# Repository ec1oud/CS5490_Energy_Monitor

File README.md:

# UEXT AC Energy Monitor module

I'm developing this for use with an 
[Olimex board](https://www.olimex.com/Products/OLinuXino/RT5350F/RT5350F-OLinuXino-EVB/open-source-hardware)
that runs [OpenWrt](https://openwrt.org/toh/olimex/rt5350f-olinuxino-evb) and
has two GPIO-controlled relays, which I'm hoping to use as a pool pump
controller.  I want to be able to monitor the performance of the pool pump over
time, because this summer it started overheating and eventually failed.  It
would be nice to get an early warning when that's about to happen.  I was
searching and it seems that the 
[CS5490](https://www.cirrus.com/products/cs5490/) will fit the bill: it's 3.3V
powered, cheap enough, doesn't require much supporting circuitry, and works
with current transformers.  The little Olimex board ought to be a good
replacement for the old PC with a DS2413 relay connected to a DS9490 USB
adapter, that has been acting as a pool pump timer (and doing some other minor
home automation tasks) for a few years.

So far I have a working breakout board, designed with 
[KiCad](http://kicad-pcb.org/), that is successfully measuring AC current.  It
has a resistive voltage divider for measuring voltage too, but there is a
safety issue: the design requires connecting DC ground to the neutral wire,
while the other end of the voltage divider goes to line voltage.  Usually
embedded systems like this are kept "floating" behind a transformer or isolated
switching power supply.  I would prefer to measure the full 240VAC that the
pool pump runs on, for accurate power computation, but of course I'm not going
to connect the DC ground of this board (and consequently the ground of the
Olimex board) to a "hot" wire.  In either case, the isolation of the Ethernet
port would depend on the fact that (hopefully) the network jack is
transformer-coupled, because I certainly wouldn't want to cause ground loop
issues on the network either.

Measuring current might be good enough to monitor my pool pump (although it's
not satisfying not to get all the measurements this chip is capable of).  But
to really use it as an energy monitor for anything other than 120VAC US-type
circuits, an isolated design is needed.  I'm thinking my options are to let the
entire CS5490 chip run from an independent power supply and use optocouplers to
isolate the serial line, so that the Olimex board can have a floating DC
ground; or, run everything from a plain old step-down transformer, measure the
AC voltage coming from the transformer (before the rectifier), and calibrate
the CS5490 so that it thinks it's measuring the full AC voltage feeding the
transformer.  An AC brownout ought to result in a proportionately lower voltage
from the transformer; and I hope there is no phase difference significant
enough to affect the power computation.

It also turns out the RT5350F-OLinuXino-EVB has a design flaw: the 
[UEXT connector](https://www.olimex.com/Products/Modules/UEXT/) has a serial
port, but it's the same one that the OpenWrt firmware is using for the Linux
console!  So I can't use those serial lines for communicating with external
hardware (which I thought is supposed to be the main purpose of a UEXT
connector) unless I alter the firmware (or at least the kernel boot parameters)
to disable the serial console, which would also amount to "bricking" the board
if anything goes wrong with the network configuration.  But there's another
serial port on the 40-pin EXT4 connector.  So I designed my board to plug into
the UEXT connector, but now I need to redesign it to plug into the 40-pin
connector instead, which makes it less portable to other embedded systems.  And
also take care of the AC isolation problem somehow.

So now you know the caveats... you'd probably better not connect the line and
neutral screw terminals to anything, unless you know what you're doing.  But
measuring current with a current transformer is pretty safe AFAIK, and works
fine with this design.  I wrote a little test GUI with Qt to communicate with
the board using an FTDI adapter or something like that.  I also wrote another
test client using Lua 5.1 on the OpenWrt firmware, but it depends on being able
to use lua-rs232 at 600 baud (the default baud rate of the CS5490's serial
lines).  See 
[the issue about that](https://github.com/openwrt/packages/issues/10024).

A design for a 3D-printable DIN rail mounting solution is also included:

The hardware design is licensed under a 

[Creative Commons Attribution-ShareAlike 4.0 International License](http://creativecommons.org/licenses/by-sa/4.0/)
.

The software has a GPLv3 license.

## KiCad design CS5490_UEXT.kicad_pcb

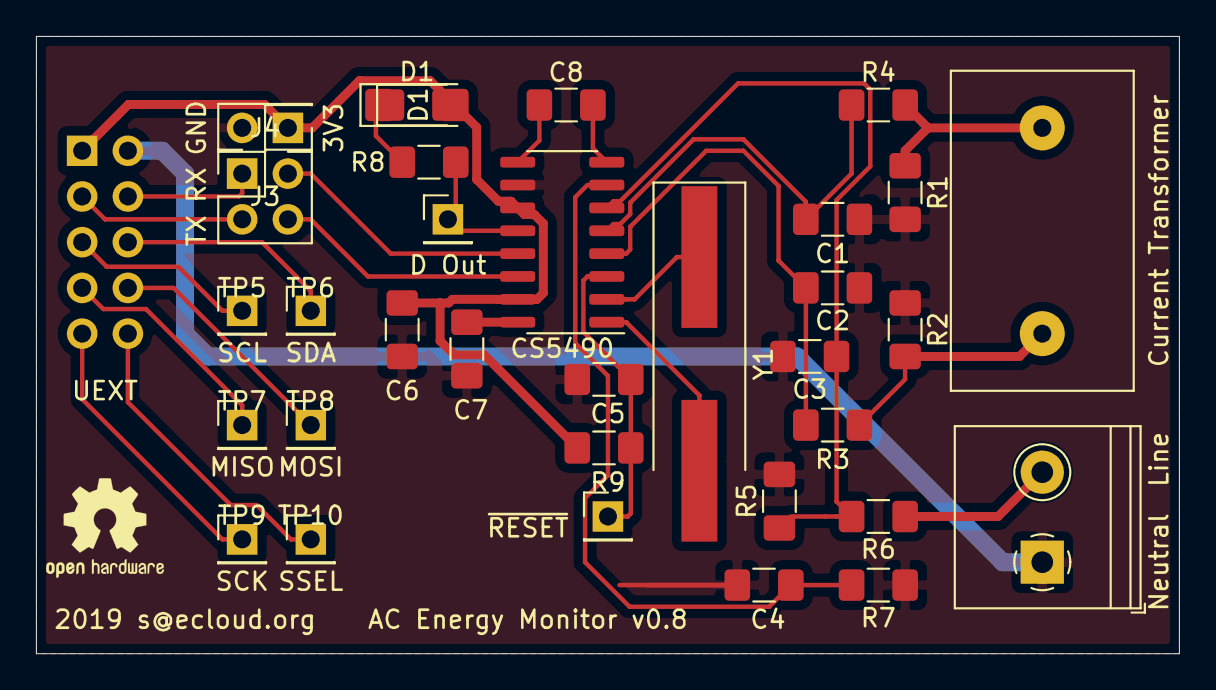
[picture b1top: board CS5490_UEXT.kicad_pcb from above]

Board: 2 copper layers, 63.5 x 34.3 mm, 34 parts (1 on the bottom side), 27 nets.

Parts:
C1, C2, C3, C4: 27nF; C_1206_3216Metric_Pad1.42x1.75mm_HandSolder
C5, C6, C7, C8: 100nF; C_1206_3216Metric_Pad1.42x1.75mm_HandSolder
CS5490: CS5490-ISZ; SOIC-16_3.9x9.9mm_P1.27mm
Current Transformer: CT; ct_11.5_mm
D1: LED_1206_3216Metric
D1#2: LED; LED_1806_4516Metric_Pad1.57x1.80mm_HandSolder
D Out: D Out; PinHeader_1x01_P2.54mm_Vertical
J1: BH10S; PinSocket_2x05_P2.54mm_Vertical
J3: serial; PinHeader_2x02_P2.54mm_Vertical
J4: Power; PinHeader_2x01_P2.54mm_Vertical
LOGO1: Logo_Open_Hardware_Small; OSHW-Logo2_7.3x6mm_SilkScreen
Line: Line; TerminalBlock_Philmore_TB132_1x02_P5.00mm_Horizontal
R1, R2: RB/2; R_1206_3216Metric_Pad1.42x1.75mm_HandSolder
R3, R4, R5, R7, R8: 1K; R_1206_3216Metric_Pad1.42x1.75mm_HandSolder
R6: 2M; R_1206_3216Metric_Pad1.42x1.75mm_HandSolder
R9: 10K; R_1206_3216Metric_Pad1.42x1.75mm_HandSolder
TP5: SCL; PinHeader_1x01_P2.54mm_Vertical
TP6: SDA; PinHeader_1x01_P2.54mm_Vertical
TP7: MISO; PinHeader_1x01_P2.54mm_Vertical
TP8: MOSI; PinHeader_1x01_P2.54mm_Vertical
TP9: SCK; PinHeader_1x01_P2.54mm_Vertical
TP10: SSEL; PinHeader_1x01_P2.54mm_Vertical
Y1: 4.096MHz; Crystal_SMD_HC49-SD_HandSoldering

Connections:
+3V3: C6.1, CS5490.11, CS5490.15, D1#2.2, J1.1, J4.1, R9.1
/Line: Line.2, R6.1
/RX: J1.4, J3.1
/TX: J1.3, J3.3
GND: C1.2, C2.1, C3.2, C4.1, C5.1, C6.2, C7.2, CS5490.10, J1.2, J4.2, Line.1, R1.2, R2.1, R5.2, R7.1
unnamed: C1.1, CS5490.5, R4.1
unnamed: C2.2, CS5490.4, R3.1
unnamed: C3.1, CS5490.6, R5.1, R6.2
unnamed: C4.2, CS5490.7, R7.2
unnamed: C5.2, CS5490.3, R9.2
unnamed: C7.1, CS5490.16
unnamed: C8.1, CS5490.9
unnamed: C8.2, CS5490.8
unnamed: D1#2.1, R8.1
unnamed: J1.5, TP5.1
unnamed: J1.6, TP6.1
unnamed: J1.7, TP7.1
unnamed: J1.8, TP8.1
unnamed: J1.9, TP9.1
unnamed: J1.10, TP10.1
unnamed: CS5490.13, J3.2
unnamed: CS5490.14, J3.4
unnamed: Current Transformer.2, R1.1, R4.2
unnamed: Current Transformer.1, R2.2, R3.2
unnamed: CS5490.12, D Out.1, R8.2
unnamed: CS5490.1, Y1.2
unnamed: CS5490.2, Y1.1

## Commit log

2019-09-18 version 0.8: working PCB; not sure whether UEXT pinout is correct/useful
    I want to use this with a RTF5350F-OLinuXino-UM; but on the evaluation
    board's UEXT port, the serial RX and TX lines are the same ones used
    for the Linux console in the OpenWRT firmware (also physically wired
    to the 3-pin UART0 port). It's thus not a good choice for connecting
    peripheral devices, because I don't want to disable the serial console
    and risk being unable to access the Linux system, in case anything
2019-09-18 Add a test client written with Lua 5.1
2019-09-18 Add a Qt Serial Port client GUI for reading values from the CS5490
    Of course the board will be used with embedded systems mainly,
    but I wanted to test it on a PC to make sure it works. Just connect
    to your FTDI or CP2102 usb->serial converter and run this to
    communicate with it at the default 600 baud.
2019-09-18 add README and a photo
2019-09-28 rearrange kicad project to enable cloning
2019-10-06 lua client: offset calibration
2019-10-06 refactor lua clients: write cs5490 module; calibration in separate file
2019-10-06 perform current gain calibration with 22Ω burden resistors
2019-10-20 perform current gain calibration with 3.3Ω burden resistors
    With 22Ω we were probably limited to around 800W max. Need to be able
    to measure way more than that, especially for peaks since the pool pump
    is an inductive load. But now it will be less accurate.
2019-10-25 Add a DIN rail sled design for mounting

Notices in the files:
README.md:
CC BY-SA 4.0
